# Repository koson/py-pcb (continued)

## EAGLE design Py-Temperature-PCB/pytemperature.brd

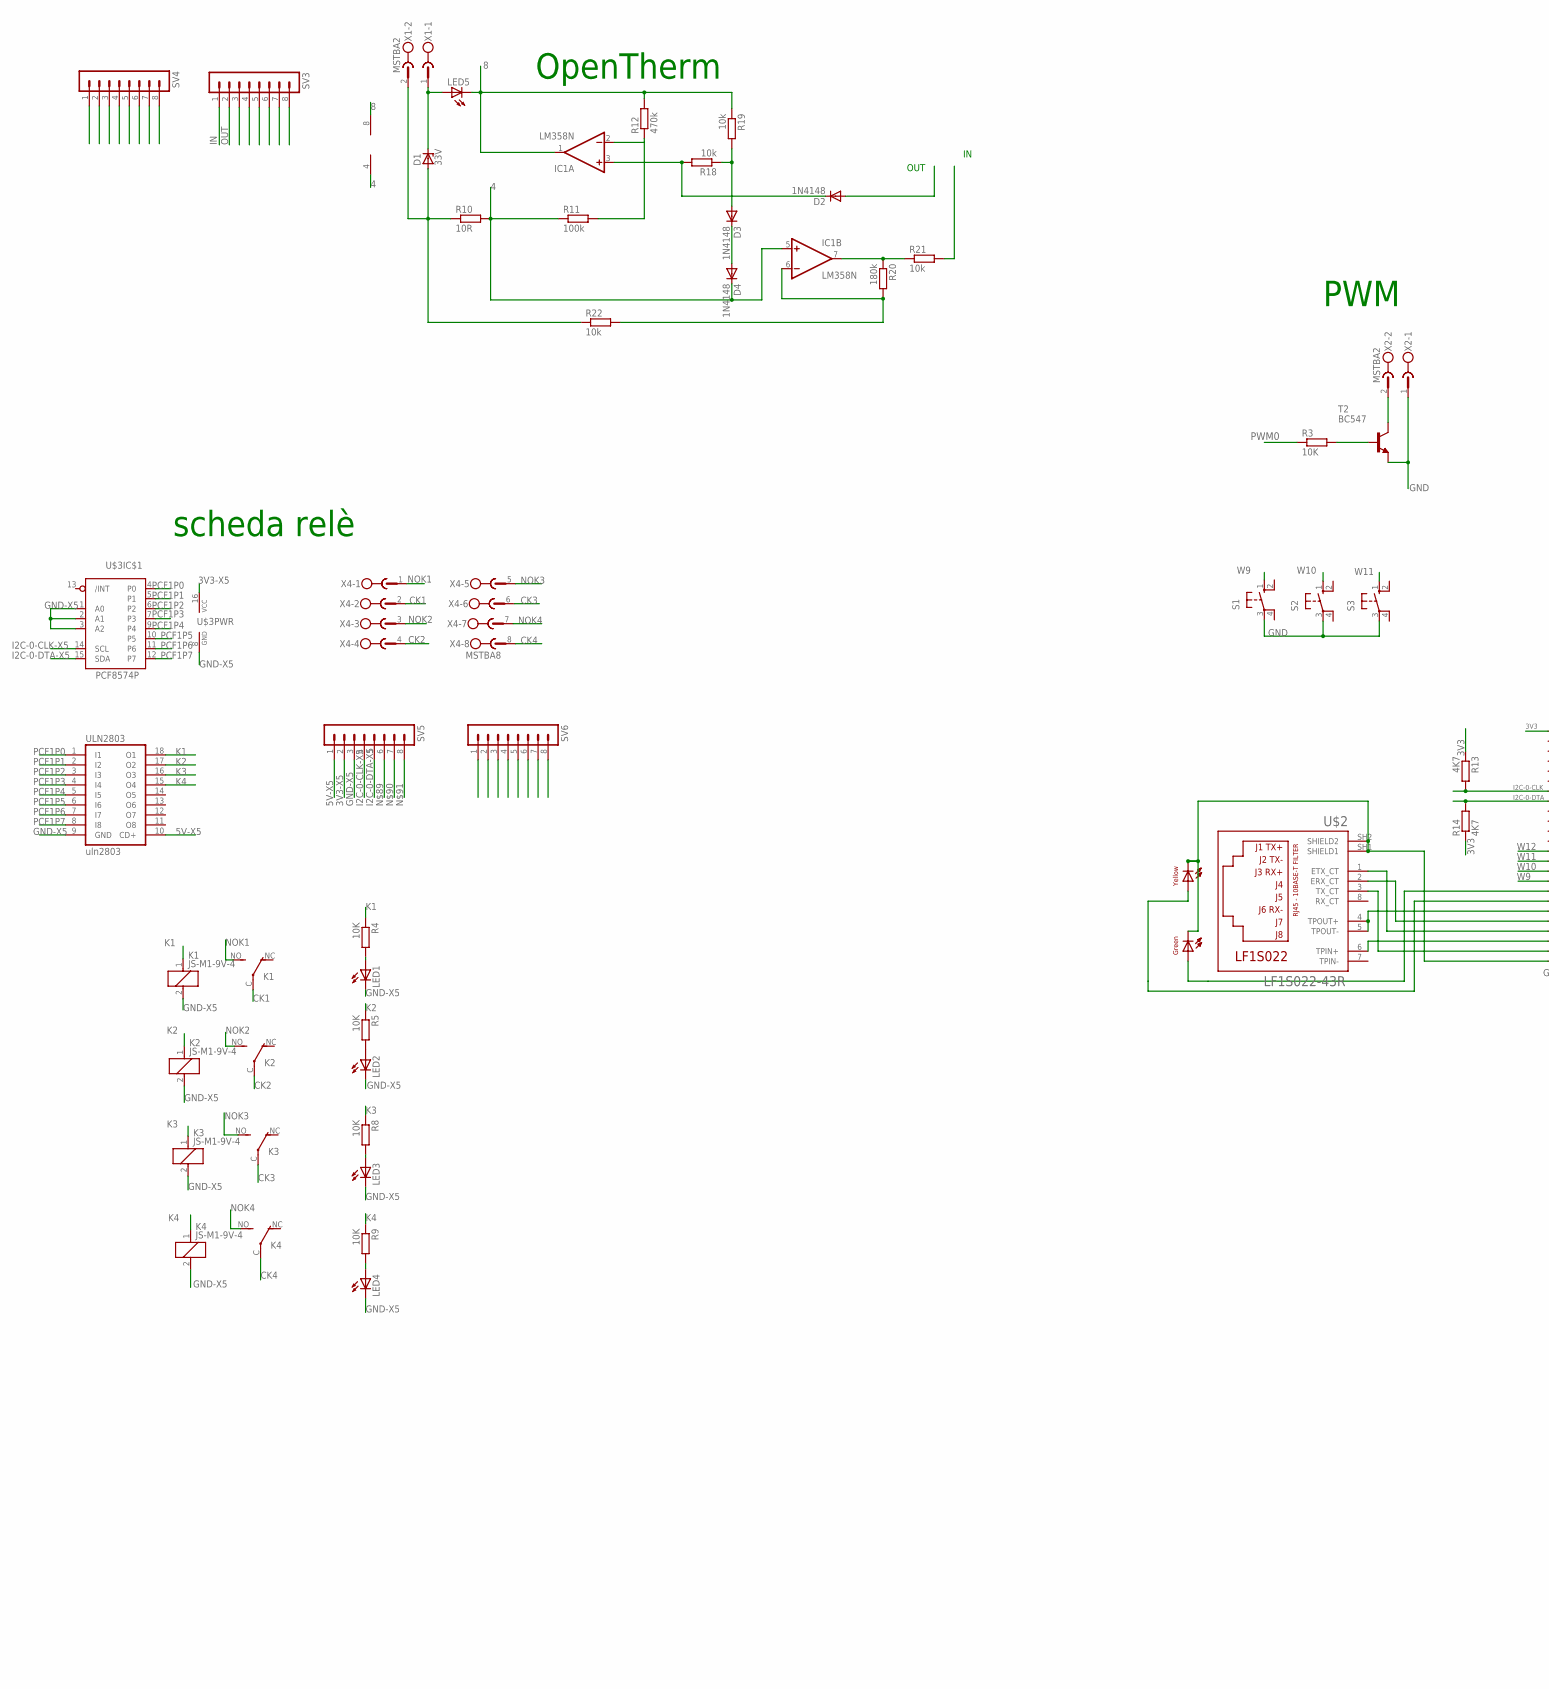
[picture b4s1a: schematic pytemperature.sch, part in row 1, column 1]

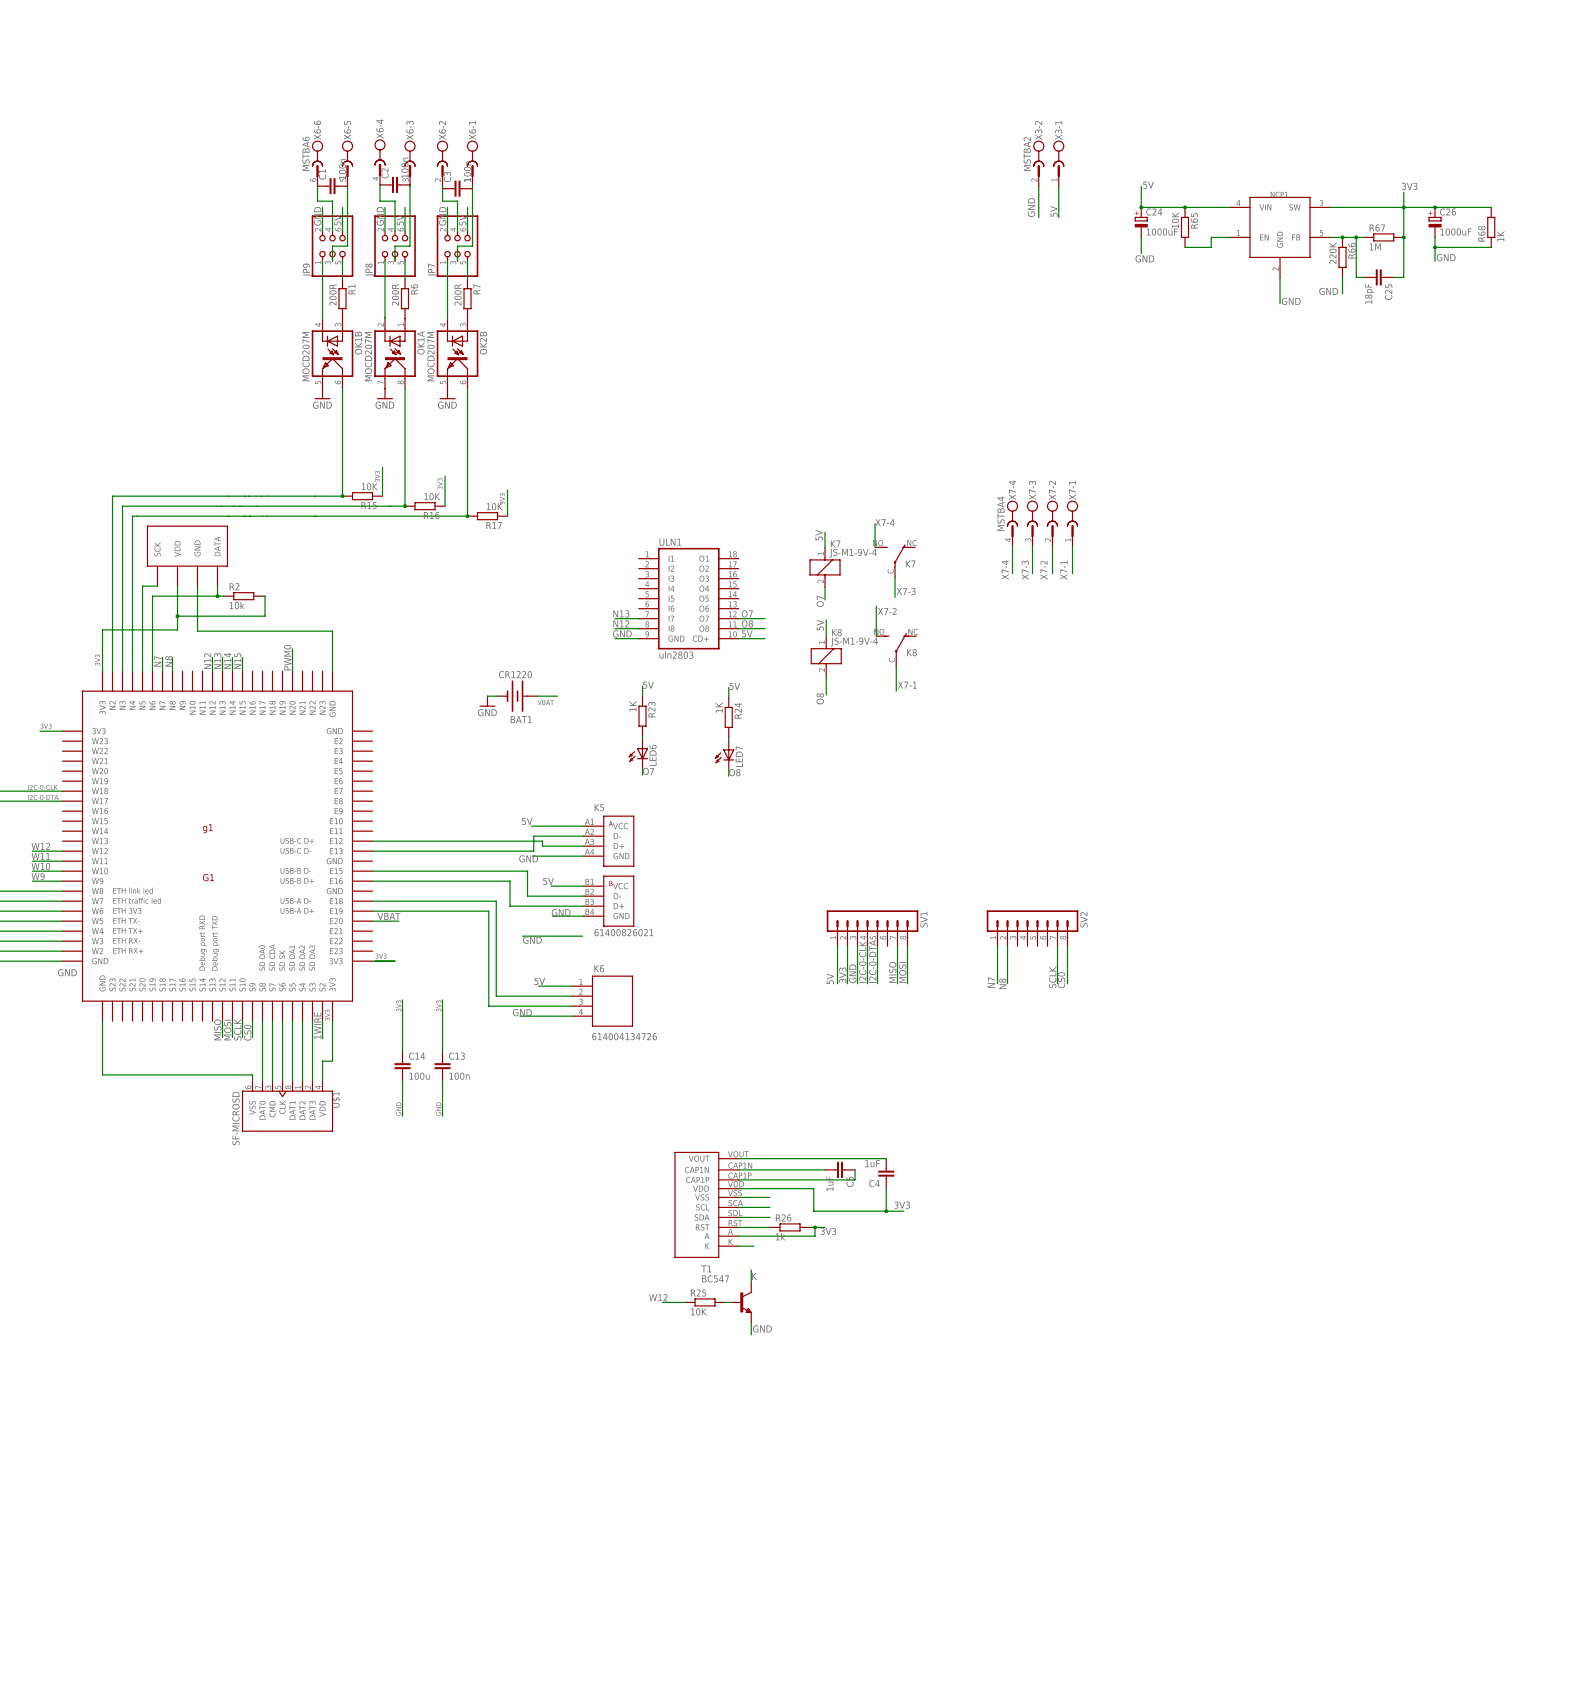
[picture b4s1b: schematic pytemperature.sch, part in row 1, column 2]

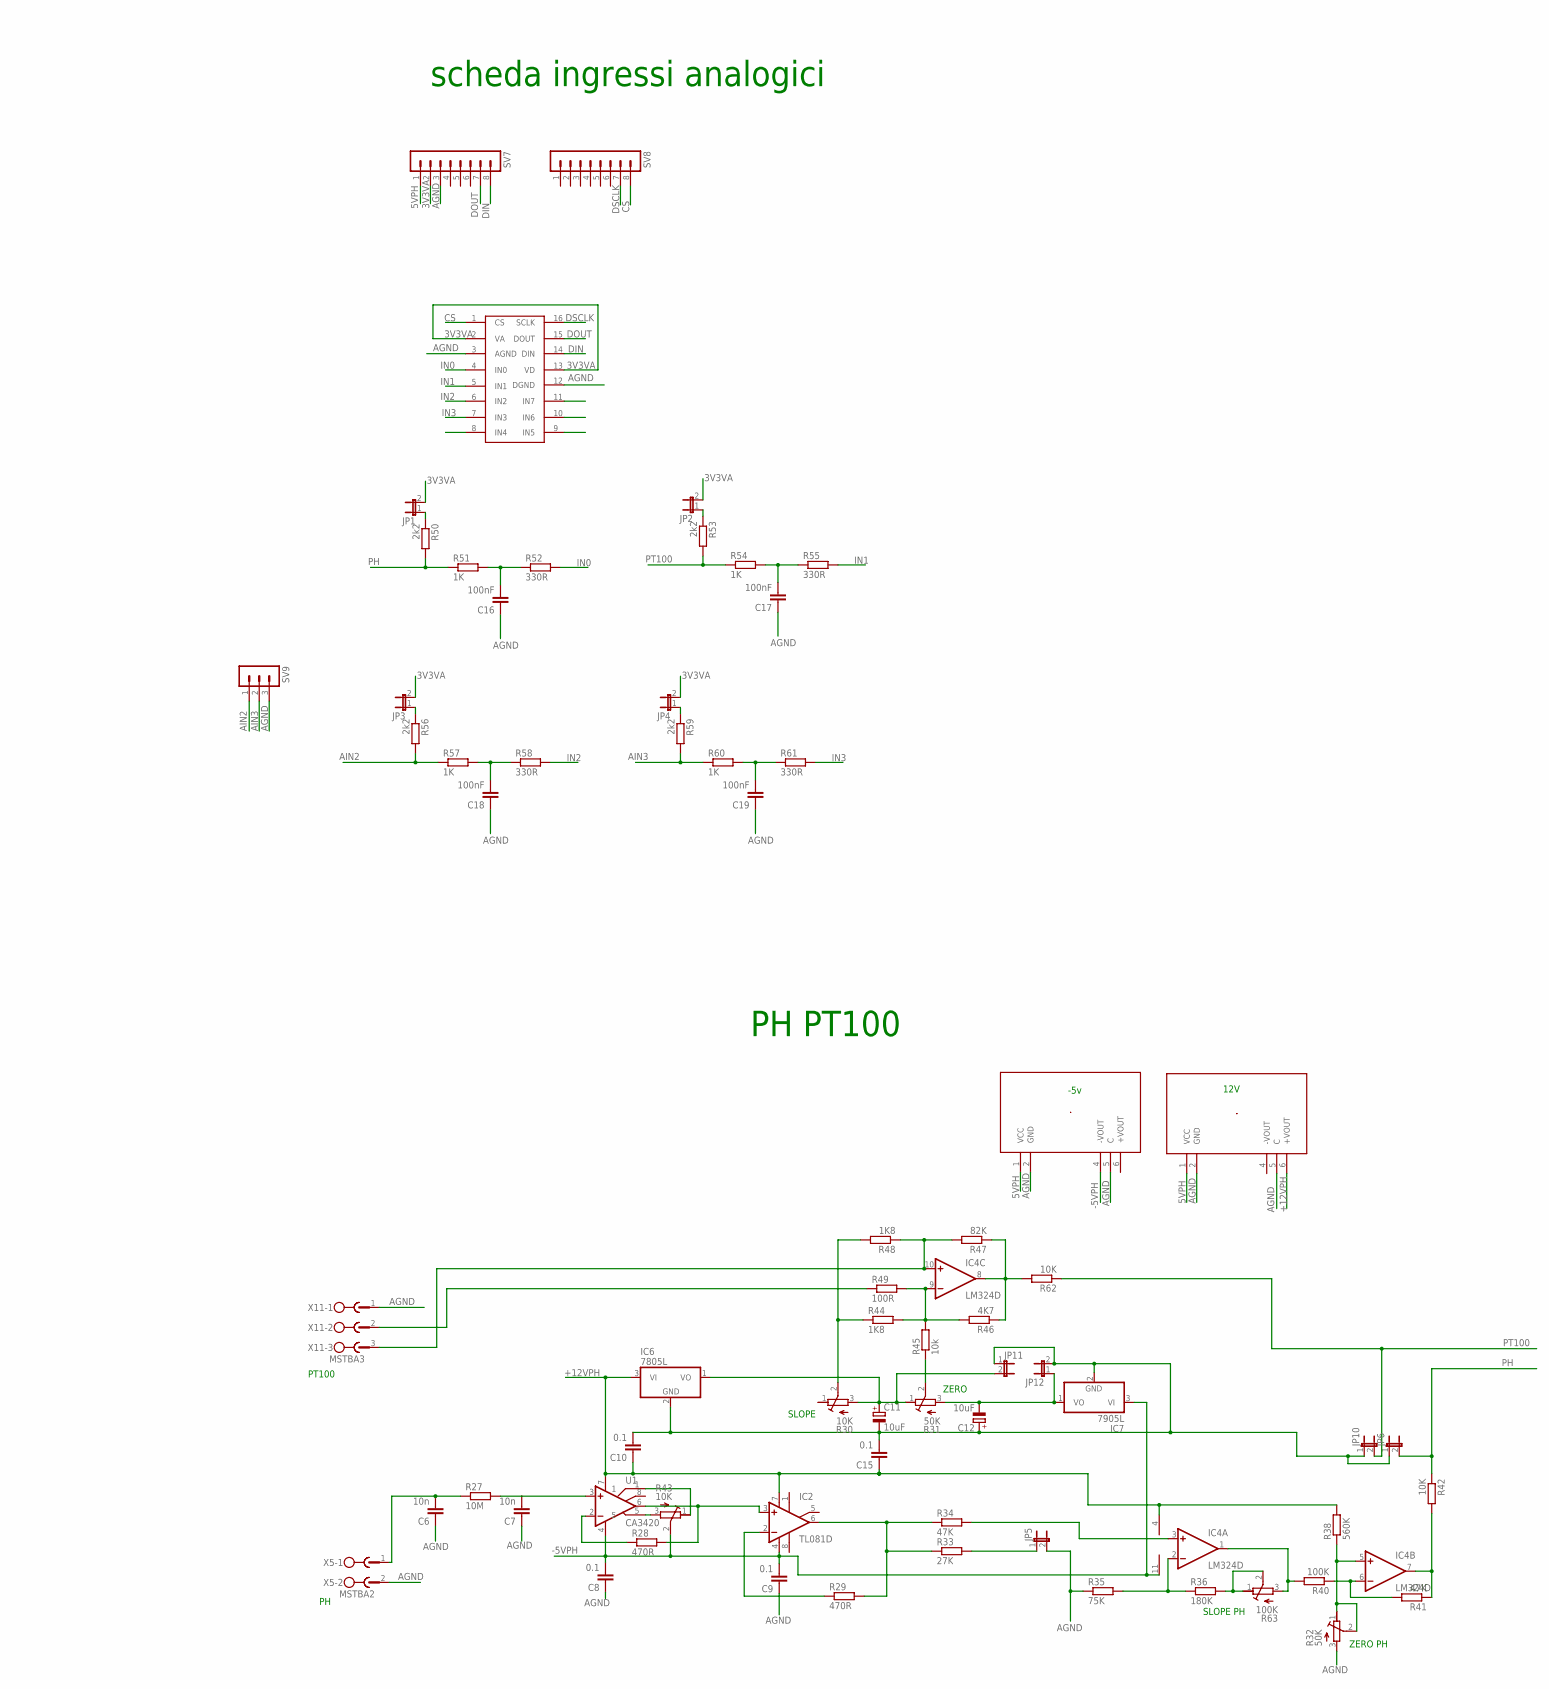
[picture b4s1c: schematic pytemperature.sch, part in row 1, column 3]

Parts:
BAT1: CR1220; BAT_CR1220
C1, C2, C3: 100n; C0805K
C4, C5: 1uF; C0805K
C6, C7: 10n; C0805K
C8, C9, C10, C15: 0.1; C0805K
C11, C12: 10uF; E3,5-8
C13: 100n; C1206K
C14: 100u; C0805K
C16, C17, C18, C19: 100nF; C0805K
C24, C26: 1000uF; E3,5-8
C25: 18pF; C0805K
D1: 33V; C1702-15
D2, D3, D4: 1N4148; DO35-10
G1: g1; G25
IC1: LM358N; DIL08
IC2: TL081D; SO08
IC4: LM324D; SO14
IC6: 7805L; TO92
IC7: 7905L; TO92
JP1, JP2, JP3, JP4, JP5, JP6, JP10, JP11, JP12: JP1E; JP1
JP7, JP8, JP9: PINHD-2X3; 2X03
K1, K2, K3, K4, K7, K8: JS-M1-9V-4; JS-M
K5: 61400826021
K6: 614004134726
LED1, LED2, LED3, LED4, LED5, LED6, LED7: LED5MM
NCP1: NCP1529; TSOP-5
OK1, OK2: MOCD207M; SOIC08-FAIRCHILD
R1, R6, R7: 200R; R0805
R2: 10k; 0204V
R3, R4, R5, R8, R9, R15, R16, R17, R25, R42, R62, R65: 10K; R0805
R10: 10R; R0805
R11: 100k; R0805
R12: 470k; R0805
R13, R14, R46: 4K7; R0805
R18, R19, R21, R22, R45: 10k; R0805
R20: 180k; R0805
R23, R24, R51, R54, R57, R60, R68: 1K; R0805
R26: 1k; R0805
R27: 10M; R0805
R28, R29: 470R; R0805
R30, R43: 10K; RTRIMT93YA
R31, R32: 50K; RTRIMT93YA
R33: 27K; R0805
R34, R41: 47K; R0805
R35: 75K; R0805
R36: 180K; R0805
R38: 560K; R0805
R40: 100K; R0805
R44, R48: 1K8; R0805
R47: 82K; R0805
R49: 100R; R0805
R50, R53, R56, R59: 2k2; R0805
R52, R55, R58, R61: 330R; R0805
R63: 100K; RTRIMT93YA
R66: 220K; R0805
R67: 1M; R0805
S1, S2, S3: 10-XX; B3F-10XX
SV1, SV2, SV3, SV4, SV5, SV6, SV7, SV8: MA08-1
SV9: MA03-1
T1, T2: BC547; TO92
U1: CA3420
U$1: SF-MICROSD; MICROSD
U$2: LF1S022-43R; LF1S022-43
U$3: PCF8574P; DIL16
U$4: LCDGIUSTO; WO1602I-TFH
U$5: ADC128S052; TSSOP16
U$6, U$8: TRACO_TMH_SERIES; TMH
U$7: SHT71; SHT7X
ULN1, ULN2803: uln2803; DIL18
X1, X2, X3, X5: MSTBA2
X4: MSTBA8
X6: MSTBA6
X7: MSTBA4
X11: MSTBA3

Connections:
1WIRE: G1.S2
3V3: C4.1, C13.1, C14.1, C25.1, C26.+, G1.E24 (3V3), G1.N1 (3V3), G1.S1 (3V3), G1.W24 (3V3), NCP1.3 (SW), R2.2, R13.1, R14.1, R15.1, R16.1, R17.1, R26.2, R67.2, R68.2, SV1.2, U$1.4 (VDD), U$4.A, U$4.VDD, U$7.2 (VDD)
3V3-X5: SV5.2, U$3.16 (VCC)
3V3VA: JP1.2, JP2.2, JP3.2, JP4.2, SV7.2, U$5.2 (VA), U$5.13 (VD)
4: D4.C, IC1.4 (V-), IC1.5 (+IN), R10.2, R11.1
5V: C24.+, JP7.6, JP8.6, JP9.6, K5.A1 (VCC), K5.B1 (VCC), K6.1, K7.1, K8.1, NCP1.4 (VIN), R23.1, R24.1, R65.1, SV1.1, ULN1.10 (CD+), X3.1
5V-X5: SV5.1, ULN2803.10 (CD+)
5VPH: SV7.1, U$6.1 (VCC), U$8.1 (VCC)
8: IC1.1 (OUT), IC1.8 (V+), LED5.K (C), R12.2, R19.1
+12VPH: C10.1, C15.1, IC2.7 (V+), IC4.4 (V+), IC6.3 (VI), R38.2, U1.7, U$8.6 (+VOUT)
-5VPH: C8.2, C9.2, IC2.4 (V-), IC4.11 (V-), IC7.3 (VI), R43.2 (S), U1.4, U$6.4 (-VOUT)
AGND: C6.1, C7.1, C8.1, C9.1, C10.2, C11.-, C12.+, C15.2, C16.1, C17.1, C18.1, C19.1, IC6.2 (GND), IC7.2 (GND), JP5.2, JP6.1, JP10.1, JP11.1, JP12.2, R32.3 (E), R35.1, SV7.3, SV9.3, U$5.3 (AGND), U$5.12 (DGND), U$6.2 (GND), U$6.5 (C), U$8.2 (GND), U$8.5 (C), X5.2, X11.1
AIN2: R56.2, R57.1, SV9.1
AIN3: R59.2, R60.1, SV9.2
CK1: K1.C, X4.2
CK2: K2.C, X4.4
CK3: K3.C, X4.6
CK4: K4.C, X4.8
CS: SV8.8, U$5.1 (CS)
CS0: G1.S9, SV2.8
DIN: SV7.8, U$5.14 (DIN)
DOUT: SV7.7, U$5.15 (DOUT)
DSCLK: SV8.7, U$5.16 (SCLK)
GND: BAT1.GND (-), C13.2, C14.2, C24.-, C26.-, G1.E1 (GND), G1.E14 (GND), G1.E17 (GND), G1.N24 (GND), G1.S24 (GND), G1.W1 (GND), JP7.2, JP8.2, JP9.2, K5.A4 (GND), K5.B4 (GND), K6.4, NCP1.2 (GND), OK1.5 (EMIT), OK1.7 (EMIT), OK2.5 (EMIT), R66.2, R68.1, S1.3, S2.3, S3.3, SV1.3, T1.1 (E), T2.1 (E), U$1.6 (VSS), U$2.10 (CG), U$2.11 (CY), U$2.SH1 (SHIELD1), U$2.SH2 (SHIELD2), U$4.VSS, U$7.3 (GND), ULN1.9 (GND), X2.1, X3.2
GND-X5: K1.2, K2.2, K3.2, K4.2, LED1.K (C), LED2.K (C), LED3.K (C), LED4.K (C), SV5.3, U$3.1 (A0), U$3.2 (A1), U$3.3 (A2), U$3.8 (GND), ULN2803.9 (GND)
I2C-0-CLK: G1.W18, R13.2, SV1.4, U$4.SCA (SCL)
I2C-0-CLK-X5: SV5.4, U$3.14 (SCL)
I2C-0-DTA: G1.W17, R14.2, SV1.5, U$4.SDL (SDA)
I2C-0-DTA-X5: SV5.5, U$3.15 (SDA)
IN: R21.2, SV3.1
IN0: R52.2, U$5.4 (IN0)
IN1: R55.2, U$5.5 (IN1)
IN2: R58.2, U$5.6 (IN2)
IN3: R61.2, U$5.7 (IN3)
IN4: U$5.8 (IN4)
IN5: U$5.9 (IN5)
IN6: U$5.10 (IN6)
IN7: U$5.11 (IN7)
K: T1.3 (C), U$4.K
K1: K1.1, R4.1, ULN2803.18 (O1)
K2: K2.1, R5.1, ULN2803.17 (O2)
K3: K3.1, R8.1, ULN2803.16 (O3)
K4: K4.1, R9.1, ULN2803.15 (O4)
LM9: R49.1, X11.2
LM10: IC4.10 (+IN), R47.2, R48.1, X11.3
MISO: G1.S12, SV1.7
MOSI: G1.S11, SV1.8
N7: G1.N7, SV2.1
N8: G1.N8, SV2.2
N12: G1.N12, ULN1.8 (I8)
N13: G1.N13, ULN1.7 (I7)
N14: G1.N14
N15: G1.N15
unnamed: G1.W2, U$2.3 (TX_CT)
unnamed: G1.W3, U$2.6 (TPIN+)
unnamed: G1.W4, U$2.1 (ETX_CT)
unnamed: G1.W5, U$2.2 (ERX_CT)
unnamed: G1.W6, U$2.4 (TPOUT+), U$2.5 (TPOUT-)
unnamed: G1.W8, U$2.9 (AG)
unnamed: G1.W7, U$2.12 (AY)
unnamed: G1.N6, R2.1, U$7.4 (DATA)
unnamed: G1.N2, OK1.6 (COL), R15.2
unnamed: G1.S6, U$1.5 (CLK)
unnamed: G1.S8, U$1.7 (DAT0)
unnamed: G1.S7, U$1.3 (CMD)
unnamed: G1.S3, U$1.2 (DAT3)
unnamed: G1.S4, U$1.1 (DAT2)
unnamed: G1.S5, U$1.8 (DAT1)
unnamed: G1.N3, OK1.8 (COL), R16.2
unnamed: G1.N4, OK2.6 (COL), R17.2
unnamed: LED6.A, R23.2
unnamed: LED7.A, R24.2
unnamed: G1.N5, U$7.1 (SCK)
unnamed: LED1.A, R4.2
unnamed: G1.E13, K5.A2 (D-)
unnamed: LED2.A, R5.2
unnamed: C12.-, IC7.1 (VO), JP12.1, R31.3 (E)
unnamed: G1.E12, K5.A3 (D+)
unnamed: LED3.A, R8.2
unnamed: LED4.A, R9.2
unnamed: G1.E18, K6.2
unnamed: G1.E19, K6.3
unnamed: JP9.1, OK1.4 (C)
unnamed: OK1.3 (A), R1.2
unnamed: JP9.5, R1.1
unnamed: JP8.1, OK1.2 (C)
unnamed: OK1.1 (A), R6.2
unnamed: JP8.5, R6.1
unnamed: JP7.1, OK2.4 (C)
unnamed: D1.C, LED5.A, X1.1
unnamed: G1.E15, K5.B2 (D-)
unnamed: G1.E16, K5.B3 (D+)
unnamed: D2.C, IC1.3 (+IN), R18.2
unnamed: C6.2, R27.1, X5.1
unnamed: OK2.3 (A), R7.2
unnamed: IC1.2 (-IN), R11.2, R12.1
unnamed: D3.A, R18.1, R19.2
unnamed: D3.C, D4.A
unnamed: IC1.7 (OUT), R20.1, R21.1
unnamed: IC1.6 (-IN), R20.2, R22.2
unnamed: C1.1, JP9.4, X6.6
unnamed: C1.2, JP9.3, X6.5
unnamed: C2.1, JP8.4, X6.4
unnamed: C2.2, JP8.3, X6.3
unnamed: C3.1, JP7.4, X6.2
unnamed: C3.2, JP7.3, X6.1
unnamed: R26.1, U$4.RST
unnamed: C5.2, U$4.CAP1N
unnamed: C7.2, R27.2, U1.3
unnamed: IC2.2 (-IN), R29.1
unnamed: R43.3 (E), U1.5
unnamed: C5.1, U$4.CAP1P
unnamed: JP7.5, R7.1
unnamed: R25.2, T1.2 (B)
unnamed: C4.2, U$4.VOUT
unnamed: IC2.3 (+IN), R28.2, U1.6
unnamed: IC4.6 (-IN), R40.1, R41.2
unnamed: IC4.9 (-IN), R44.2, R45.2, R46.2, R49.2
unnamed: R43.1 (A), U1.1
unnamed: R28.1, U1.2
unnamed: R36.2, R63.1 (A), R63.2 (S)
unnamed: IC4.8 (OUT), R46.1, R47.1, R62.2
unnamed: JP5.1, R33.2
unnamed: IC2.6 (OUT), R29.2, R33.1, R34.1
unnamed: IC4.3 (+IN), R34.2
unnamed: IC4.7 (OUT), R41.1, R42.2
unnamed: C11.+, IC6.1 (VO), JP11.2, R30.3 (E), R31.1 (A)
unnamed: T2.3 (C), X2.2
unnamed: IC4.1 (OUT), R40.2, R63.3 (E)
unnamed: IC4.5 (+IN), R32.1 (A), R32.2 (S), R38.1
unnamed: R3.2, T2.2 (B)
unnamed: JP1.1, R50.1
unnamed: IC4.2 (-IN), R35.2, R36.1
unnamed: JP2.1, R53.1
unnamed: NCP1.1 (EN), R65.2
unnamed: C25.2, NCP1.5 (FB), R66.1, R67.1
unnamed: R30.2 (S), R44.1, R48.2
unnamed: R31.2 (S), R45.1
unnamed: C16.2, R51.2, R52.1
unnamed: C17.2, R54.2, R55.1
unnamed: JP3.1, R56.1
unnamed: C18.2, R57.2, R58.1
unnamed: JP4.1, R59.1
unnamed: C19.2, R60.2, R61.1
NOK1: K1.NO (S), X4.1
NOK2: K2.NO (S), X4.3
NOK3: K3.NO (S), X4.5
NOK4: K4.NO (S), X4.7
O7: K7.2, LED6.K (C), ULN1.12 (O7)
O8: K8.2, LED7.K (C), ULN1.11 (O8)
OGND: D1.A, R10.1, R22.1, X1.2
OUT: D2.A, SV3.2
PCF1P0: U$3.4 (P0), ULN2803.1 (I1)
PCF1P1: U$3.5 (P1), ULN2803.2 (I2)
PCF1P2: U$3.6 (P2), ULN2803.3 (I3)
PCF1P3: U$3.7 (P3), ULN2803.4 (I4)
PCF1P4: U$3.9 (P4), ULN2803.5 (I5)
PCF1P5: U$3.10 (P5), ULN2803.6 (I6)
PCF1P6: U$3.11 (P6), ULN2803.7 (I7)
PCF1P7: U$3.12 (P7), ULN2803.8 (I8)
PH: JP6.2, R42.1, R50.2, R51.1
PT100: JP10.2, R53.2, R54.1, R62.1
PWM0: G1.N20, R3.1
SCLK: G1.S10, SV2.7
VBAT: BAT1.V+ (+), G1.E20
W9: G1.W9, S1.1 (S)
W10: G1.W10, S2.1 (S)
W11: G1.W11, S3.1 (S)
W12: G1.W12, R25.1
X7-1: K8.C, X7.1
X7-2: K8.NO (S), X7.2
X7-3: K7.C, X7.3
X7-4: K7.NO (S), X7.4

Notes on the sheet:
OpenTherm
OUT
scheda relè
scheda ingressi analogici
PH PT100
12V
-5v
PT100
SLOPE
ZERO
SLOPE PH
ZERO PH
PWM

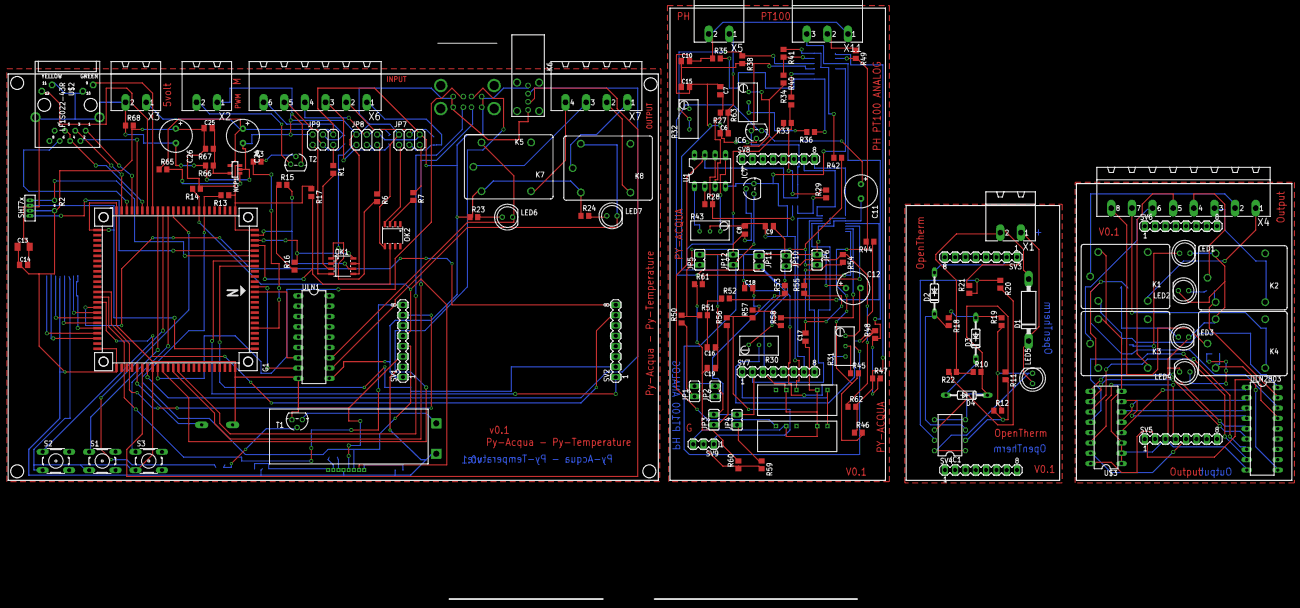
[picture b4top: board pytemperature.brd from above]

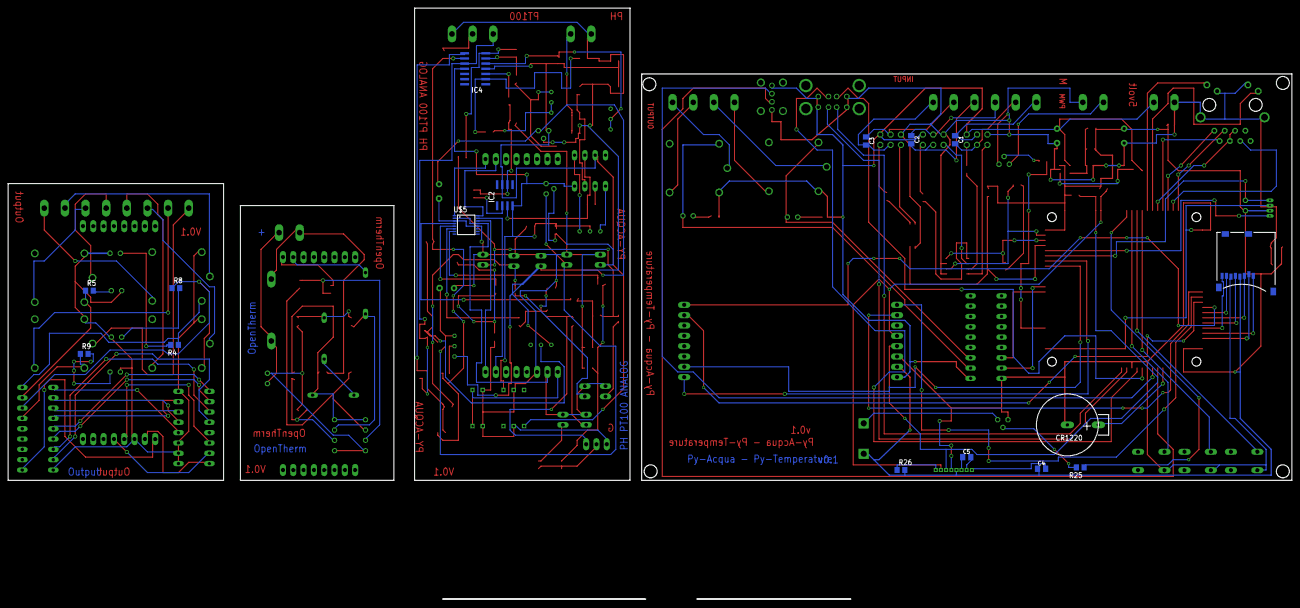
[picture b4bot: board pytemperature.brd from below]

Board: 2 copper layers, 315.9 x 145.4 mm, 161 parts (16 on the bottom side), 166 nets.

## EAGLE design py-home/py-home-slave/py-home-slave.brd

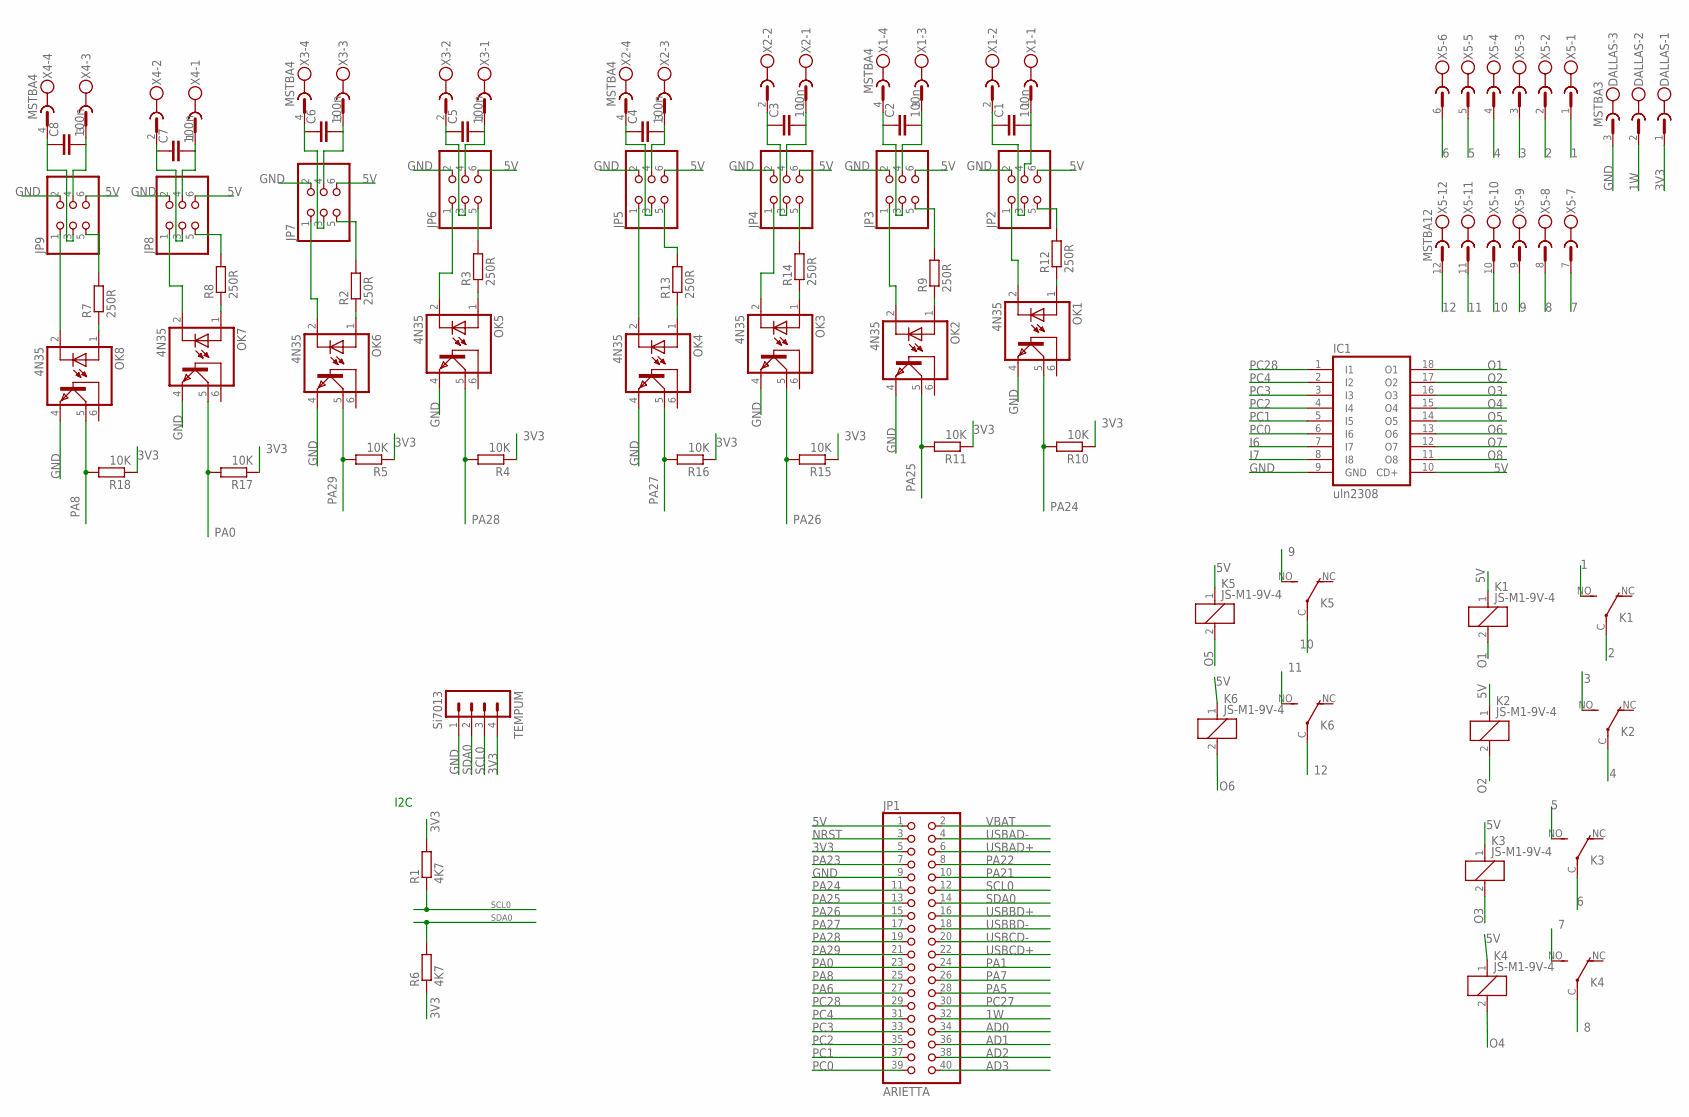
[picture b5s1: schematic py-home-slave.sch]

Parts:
C1, C2, C3, C4, C5, C6, C7, C8: 100n; C2.5-3
DALLAS: MSTBA3
IC1: uln2308; DIL18
JP1: ARIETTA; 2X20
JP2, JP3, JP4, JP5, JP6, JP7, JP8, JP9: PINHD-2X3; 2X03
K1, K2, K3, K4, K5, K6: JS-M1-9V-4; JS-M
OK1, OK2, OK3, OK4, OK5, OK6, OK7, OK8: 4N35; DIL06
R1, R6: 4K7; 0204V
R2, R3, R7, R8, R9, R12, R13, R14: 250R; 0204V
R4, R5, R10, R11, R15, R16, R17, R18: 10K; 0204V
TEMPUM: Si7013; MA04-1
X1, X2, X3, X4: MSTBA4
X5: MSTBA12

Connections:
1: K1.NO (S), X5.1
1W: DALLAS.2, JP1.32
2: K1.C, X5.2
3: K2.NO (S), X5.3
3V3: DALLAS.1, JP1.5, R1.2, R4.1, R5.1, R6.1, R10.1, R11.1, R15.1, R16.1, R17.1, R18.1, TEMPUM.4
4: K2.C, X5.4
5: K3.NO (S), X5.5
5V: IC1.10 (CD+), JP1.1, JP2.6, JP3.6, JP4.6, JP5.6, JP6.6, JP7.6, JP8.6, JP9.6, K1.1, K2.1, K3.1, K4.1, K5.1, K6.1
6: K3.C, X5.6
7: K4.NO (S), X5.7
8: K4.C, X5.8
9: K5.NO (S), X5.9
10: K5.C, X5.10
11: K6.NO (S), X5.11
12: K6.C, X5.12
AD0: JP1.34
AD1: JP1.36
AD2: JP1.38
AD3: JP1.40
GND: DALLAS.3, IC1.9 (GND), JP1.9, JP2.2, JP3.2, JP4.2, JP5.2, JP6.2, JP7.2, JP8.2, JP9.2, OK1.4 (EMI), OK2.4 (EMI), OK3.4 (EMI), OK4.4 (EMI), OK5.4 (EMI), OK6.4 (EMI), OK7.4 (EMI), OK8.4 (EMI), TEMPUM.1
I6: IC1.7 (I7)
I7: IC1.8 (I8)
unnamed: OK2.1 (A), R9.1
unnamed: C1.2, JP2.4, X1.1
unnamed: OK1.1 (A), R12.1
unnamed: JP2.1, OK1.2 (C)
unnamed: C5.1, JP6.3, X3.2
unnamed: OK6.1 (A), R2.1
unnamed: JP3.5, R9.2
unnamed: JP6.1, OK5.2 (C)
unnamed: C3.1, JP4.3, X2.2
unnamed: JP3.1, OK2.2 (C)
unnamed: OK4.1 (A), R13.1
unnamed: JP4.1, OK3.2 (C)
unnamed: OK3.1 (A), R14.1
unnamed: C4.1, JP5.3, X2.4
unnamed: JP5.1, OK4.2 (C)
unnamed: OK5.1 (A), R3.1
unnamed: C6.1, JP7.3, X3.4
unnamed: JP7.1, OK6.2 (C)
unnamed: C7.1, JP8.3, X4.2
unnamed: OK8.1 (A), R7.1
unnamed: JP8.1, OK7.2 (C)
unnamed: OK7.1 (A), R8.1
unnamed: C8.1, JP9.3, X4.4
unnamed: JP9.1, OK8.2 (C)
unnamed: JP2.5, R12.2
unnamed: C2.2, JP3.4, X1.3
unnamed: C1.1, JP2.3, X1.2
unnamed: C2.1, JP3.3, X1.4
unnamed: C3.2, JP4.4, X2.1
unnamed: JP4.5, R14.2
unnamed: JP5.5, R13.2
unnamed: JP6.5, R3.2
unnamed: JP7.5, R2.2
unnamed: C4.2, JP5.4, X2.3
unnamed: C5.2, JP6.4, X3.1
unnamed: C8.2, JP9.4, X4.3
unnamed: JP8.5, R8.2
unnamed: C6.2, JP7.4, X3.3
unnamed: C7.2, JP8.4, X4.1
unnamed: JP9.5, R7.2
NRST: JP1.3
O1: IC1.18 (O1), K1.2
O2: IC1.17 (O2), K2.2
O3: IC1.16 (O3), K3.2
O4: IC1.15 (O4), K4.2
O5: IC1.14 (O5), K5.2
O6: IC1.13 (O6), K6.2
O7: IC1.12 (O7)
O8: IC1.11 (O8)
PA0: JP1.23, OK7.5 (COL), R17.2
PA1: JP1.24
PA5: JP1.28
PA6: JP1.27
PA7: JP1.26
PA8: JP1.25, OK8.5 (COL), R18.2
PA21: JP1.10
PA22: JP1.8
PA23: JP1.7
PA24: JP1.11, OK1.5 (COL), R10.2
PA25: JP1.13, OK2.5 (COL), R11.2
PA26: JP1.15, OK3.5 (COL), R15.2
PA27: JP1.17, OK4.5 (COL), R16.2
PA28: JP1.19, OK5.5 (COL), R4.2
PA29: JP1.21, OK6.5 (COL), R5.2
PC0: IC1.6 (I6), JP1.39
PC1: IC1.5 (I5), JP1.37
PC2: IC1.4 (I4), JP1.35
PC3: IC1.3 (I3), JP1.33
PC4: IC1.2 (I2), JP1.31
PC27: JP1.30
PC28: IC1.1 (I1), JP1.29
SCL0: JP1.12, R1.1, TEMPUM.3
SDA0: JP1.14, R6.2, TEMPUM.2
USBAD+: JP1.6
USBAD-: JP1.4
USBBD+: JP1.16
USBBD-: JP1.18
USBCD+: JP1.22
USBCD-: JP1.20
VBAT: JP1.2

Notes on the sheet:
I2C

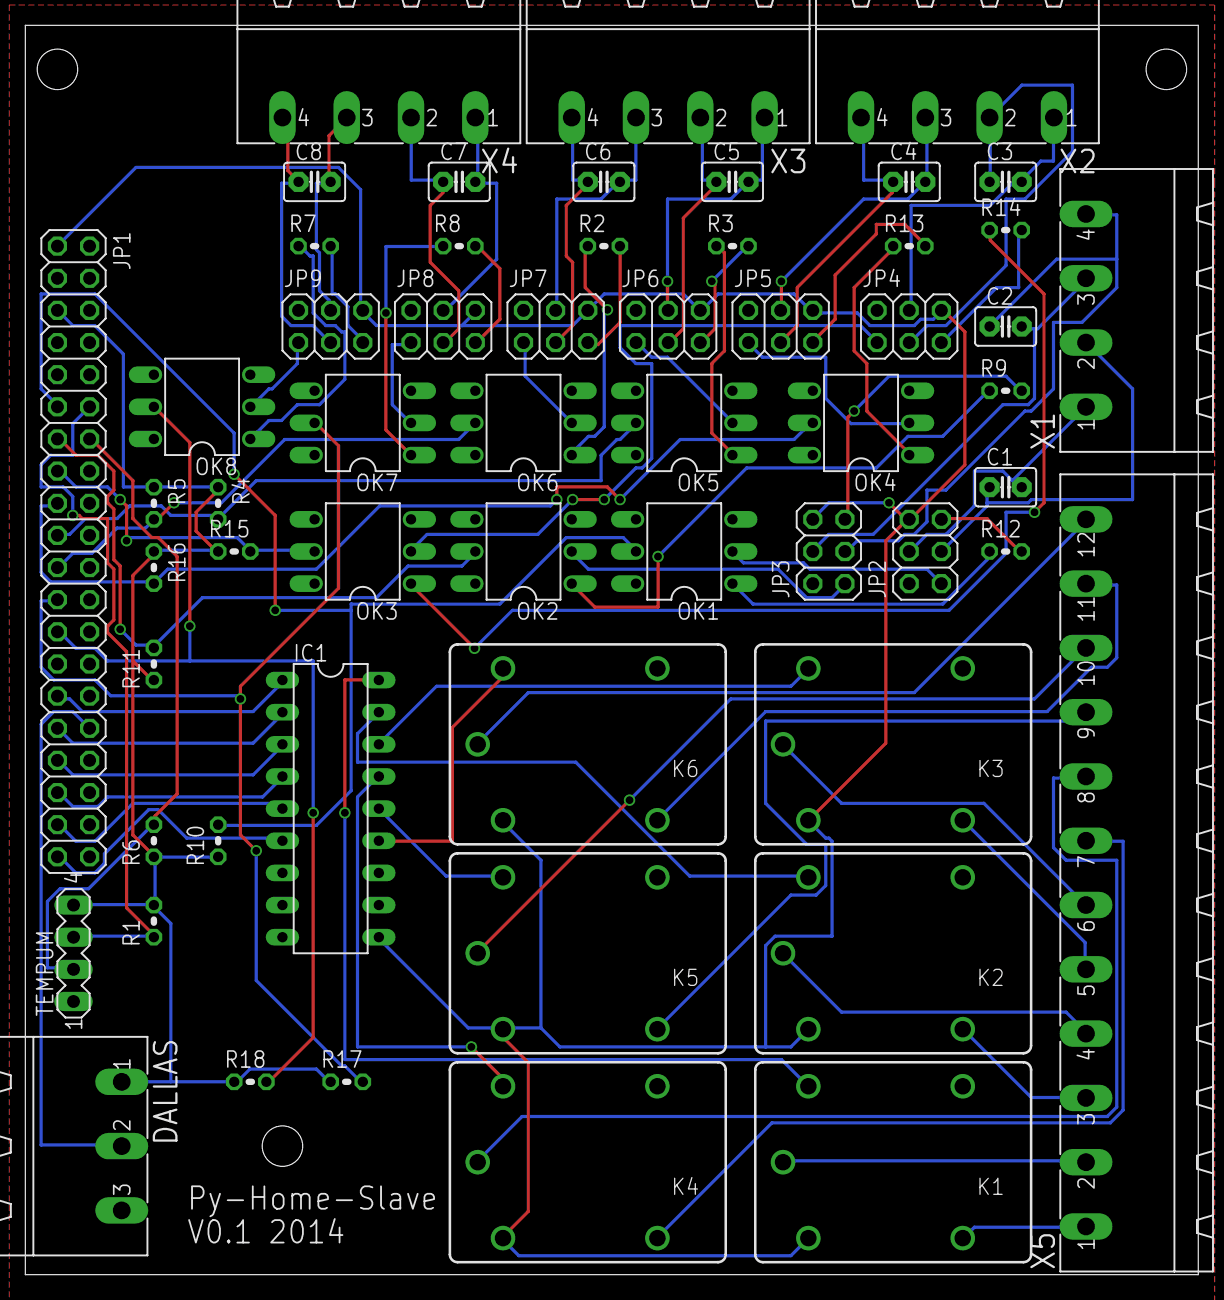
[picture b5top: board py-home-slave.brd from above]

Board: 2 copper layers, 92.7 x 98.7 mm, 57 parts (0 on the bottom side), 78 nets.

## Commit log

2016-01-29 aggiunti file su git
2016-01-29 aggiunto porta usb
2016-01-29 modifica griglia
2016-02-17 aggiunto py-home-slave a 3 rele per tende e tapparelle
2016-03-01 sistemazione pcb 3 rele
2016-11-18 sistemazioni input su py-acqua
2023-02-16 add kicad
